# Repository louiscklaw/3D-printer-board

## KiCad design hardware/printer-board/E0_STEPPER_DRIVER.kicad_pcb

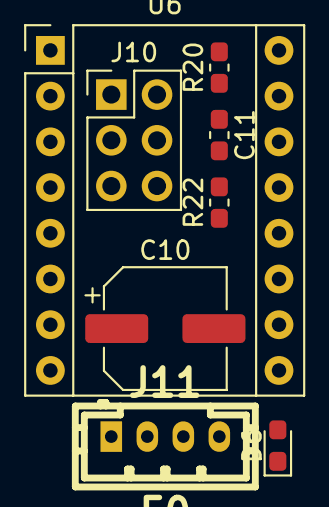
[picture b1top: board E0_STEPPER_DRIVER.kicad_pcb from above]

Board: 2 copper layers, 9 parts (1 on the bottom side), 13 nets, no tracks yet.

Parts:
C10: CP100uf,25V; CP_Elec_6.3x7.7
C11: C104,0603; C_0603_1608Metric_Pad1.05x0.95mm_HandSolder
D6: LED_BLUE,0603; LED_0603_1608Metric_Pad1.05x0.95mm_HandSolder
J10: MS_SELECT; PinHeader_2x03_P2.54mm_Vertical
J11: E0; b4b-ph-kl,stepper_terminal
R20: R104,0603; R_0603_1608Metric_Pad1.05x0.95mm_HandSolder
R21: R102,0603; R_0603_1608Metric_Pad1.05x0.95mm_HandSolder
R22: R103,0603; R_0603_1608Metric_Pad1.05x0.95mm_HandSolder
U6: A4988_MODULE; Pololu_Breakout-16_15.2x20.3mm

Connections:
+3V3_STM32: C11.2, J10.2, J10.4, J10.6, R21.1, R22.1, U6.10
+12V: C10.1, U6.16
/~E0_EN~: D6.1, R22.2, U6.1
GND: C10.2, C11.1, R20.1, U6.9, U6.15
unnamed: D6.2, R21.2
unnamed: J10.1, R20.2, U6.2
unnamed: J10.3, U6.3
unnamed: J10.5, U6.4
unnamed: J11.1, U6.14
unnamed: J11.2, U6.13
unnamed: J11.3, U6.12
unnamed: J11.4, U6.11
unnamed: U6.5, U6.6

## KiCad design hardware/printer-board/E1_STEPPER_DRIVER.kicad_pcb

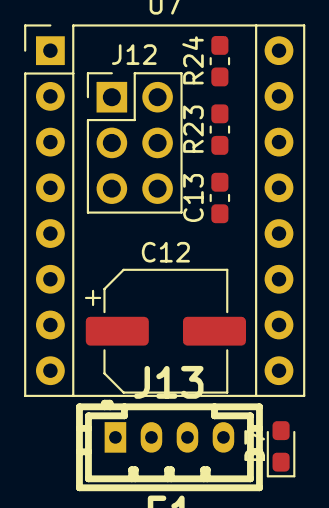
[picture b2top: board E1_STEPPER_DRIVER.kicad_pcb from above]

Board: 2 copper layers, 9 parts (1 on the bottom side), 13 nets, no tracks yet.

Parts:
C12: CP100uf,25V; CP_Elec_6.3x7.7
C13: C104,0603; C_0603_1608Metric_Pad1.05x0.95mm_HandSolder
D7: LED_BLUE,0603; LED_0603_1608Metric_Pad1.05x0.95mm_HandSolder
J12: MS_SELECT; PinHeader_2x03_P2.54mm_Vertical
J13: E1; b4b-ph-kl,stepper_terminal
R23: R104,0603; R_0603_1608Metric_Pad1.05x0.95mm_HandSolder
R24: R102,0603; R_0603_1608Metric_Pad1.05x0.95mm_HandSolder
R25: R103,0603; R_0603_1608Metric_Pad1.05x0.95mm_HandSolder
U7: A4988_MODULE; Pololu_Breakout-16_15.2x20.3mm

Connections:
+3V3_STM32: C13.2, J12.2, J12.4, J12.6, R24.1, R25.1, U7.10
+12V: C12.1, U7.16
/~E1_EN~: D7.1, R25.2, U7.1
GND: C12.2, C13.1, R23.1, U7.9, U7.15
unnamed: D7.2, R24.2
unnamed: J12.1, R23.2, U7.2
unnamed: J12.3, U7.3
unnamed: J12.5, U7.4
unnamed: J13.1, U7.14
unnamed: J13.2, U7.13
unnamed: J13.3, U7.12
unnamed: J13.4, U7.11
unnamed: U7.5, U7.6

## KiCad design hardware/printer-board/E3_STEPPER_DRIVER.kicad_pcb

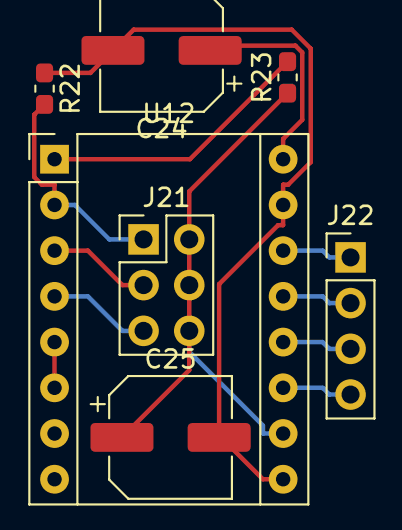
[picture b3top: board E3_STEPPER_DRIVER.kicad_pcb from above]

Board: 2 copper layers, 7 parts (0 on the bottom side), 12 nets.

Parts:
C24, C25: CP100uf,25V; CP_Elec_6.3x7.7
J21: MS_SELECT; PinHeader_2x03_P2.54mm_Vertical
J22: TO_MOTOR; PinHeader_1x04_P2.54mm_Vertical
R22: R104,0603; R_0603_1608Metric_Pad1.05x0.95mm_HandSolder
R23: R103,0603; R_0603_1608Metric_Pad1.05x0.95mm_HandSolder
U12: A4988_MODULE; Pololu_Breakout-16_15.2x20.3mm

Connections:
+5V: C25.1, J21.2, J21.4, J21.6, R23.1, U12.10
+12V: C24.1, U12.16
/~EN~: R23.2, U12.1
GND: C24.2, C25.2, R22.1, U12.9, U12.15
unnamed: J21.1, R22.2, U12.2
unnamed: J21.3, U12.3
unnamed: J21.5, U12.4
unnamed: J22.1, U12.14
unnamed: J22.2, U12.13
unnamed: J22.3, U12.12
unnamed: J22.4, U12.11
unnamed: U12.5, U12.6

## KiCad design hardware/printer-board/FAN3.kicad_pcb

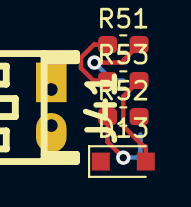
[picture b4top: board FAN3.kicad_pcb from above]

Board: 2 copper layers, 6 parts (1 on the bottom side), 4 nets.

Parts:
D13: 1N4148; D_SOD-323_HandSoldering
J41: TO FAN4; s2b-ph-kl,fan_output
Q1: SS9013_J3; SOT-23_Handsoldering
R51: R331; R_0603_1608Metric_Pad1.05x0.95mm_HandSolder
R52: R471; R_0603_1608Metric_Pad1.05x0.95mm_HandSolder
R53: R103; R_0603_1608Metric_Pad1.05x0.95mm_HandSolder

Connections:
/FAN_PWM_OUTPUT: Q1.3, R51.2
/STM32_FAN_RPM: D13.2, R53.2
unnamed: Q1.1, R52.1
VDD: R51.1, R53.1

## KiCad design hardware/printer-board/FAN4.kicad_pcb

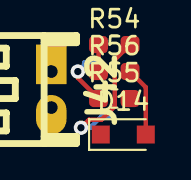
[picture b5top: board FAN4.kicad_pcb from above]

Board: 2 copper layers, 6 parts (1 on the bottom side), 4 nets.

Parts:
D14: 1N4148; D_SOD-323_HandSoldering
J42: TO FAN5; s2b-ph-kl,fan_output
Q1: SS9013_J3; SOT-23_Handsoldering
R54: R331; R_0603_1608Metric_Pad1.05x0.95mm_HandSolder
R55: R471; R_0603_1608Metric_Pad1.05x0.95mm_HandSolder
R56: R103; R_0603_1608Metric_Pad1.05x0.95mm_HandSolder

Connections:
/FAN_PWM_OUTPUT: Q1.3, R54.2
/STM32_FAN_RPM: D14.2, R56.2
unnamed: Q1.1, R55.1
VDD: R54.1, R56.1

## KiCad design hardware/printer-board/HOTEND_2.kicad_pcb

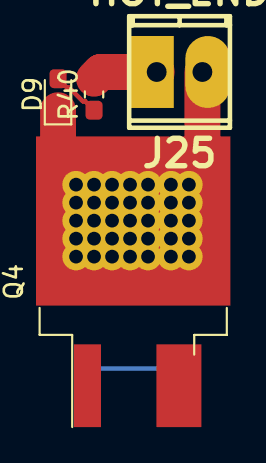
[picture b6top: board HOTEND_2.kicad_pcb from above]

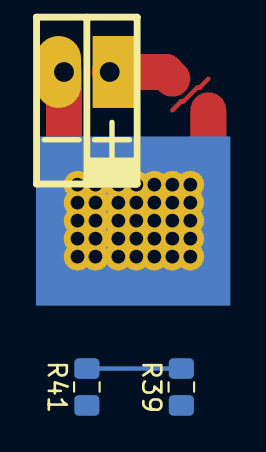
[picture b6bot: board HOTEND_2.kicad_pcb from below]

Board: 2 copper layers, 6 parts (2 on the bottom side), 6 nets.

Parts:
D9: LED_RED,0603; LED_0603_1608Metric_Pad1.05x0.95mm_HandSolder
J25: HOT_END; mpt_0,5%2f2-2,54,heatbed
Q4: WSK220N04; TO-263-2,drill_array
R39: R100,0805; R_0805_2012Metric_Pad1.15x1.40mm_HandSolder
R40: R182,0603; R_0603_1608Metric_Pad1.05x0.95mm_HandSolder
R41: R104,0805; R_0805_2012Metric_Pad1.15x1.40mm_HandSolder

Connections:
+12V: J25.1, R40.2
/-12V: D9.1, J25.2, Q4.2
/HOTEND_EN: R39.2, R41.2
GND: Q4.3, R41.1
unnamed: D9.2, R40.1
unnamed: Q4.1, R39.1

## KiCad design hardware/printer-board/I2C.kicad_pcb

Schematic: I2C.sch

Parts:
J37: Conn_01x04; PinHeader_1x04_P2.54mm_Vertical
R36, R37: R472,0603; R_0603_1608Metric_Pad1.05x0.95mm_HandSolder

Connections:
+5V: J37.1, R36.1, R37.1
/SCL: J37.4, R37.2
/SDA: J37.3, R36.2
GND: J37.2

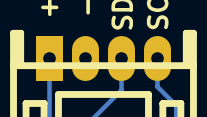
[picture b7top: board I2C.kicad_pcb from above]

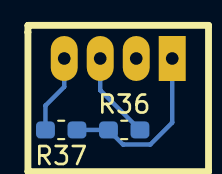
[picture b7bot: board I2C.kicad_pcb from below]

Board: 2 copper layers, 3 parts (2 on the bottom side), 3 nets.

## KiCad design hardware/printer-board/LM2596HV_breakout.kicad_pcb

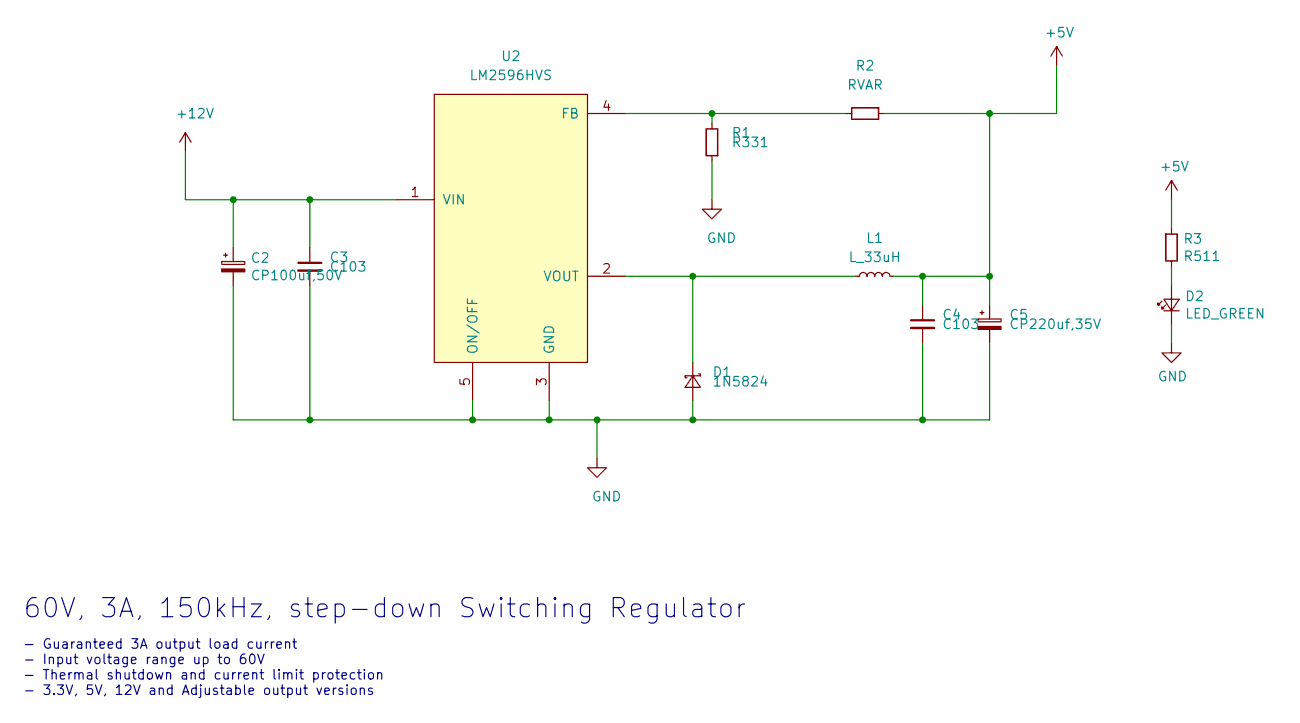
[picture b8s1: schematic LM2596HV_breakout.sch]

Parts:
C2: CP100uf,50V; C_0805_2012Metric_Pad1.15x1.40mm_HandSolder
C3: C103; C_0805_2012Metric_Pad1.15x1.40mm_HandSolder
C4: C103; c_elec_8x10.5
C5: CP220uf,35V; c_elec_8x10.5
D1: 1N5824; do214ac
D2: LED_GREEN; LED_0805_2012Metric_Pad1.15x1.40mm_HandSolder
L1: L_33uH; inductor_smd_12.5x7.5mm
R1: R331; R_0805_2012Metric_Pad1.15x1.40mm_HandSolder
R2: RVAR; R_0805_2012Metric_Pad1.15x1.40mm_HandSolder
R3: R511; R_0805_2012Metric_Pad1.15x1.40mm_HandSolder
U2: LM2596HVS; TO-263-5_TabPin3

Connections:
+5V: C4.1, C5.1, L1.2, R2.1, R3.1; also elsewhere on the board
+12V: C2.1, C3.1, U2.1 (VIN)
GND: C2.2, C3.2, C4.2, C5.2, D1.2 (A), D2.1 (K), R1.1, U2.3 (GND), U2.5 (ON/OFF); also elsewhere on the board
unnamed: D1.1 (K), L1.1, U2.2 (VOUT)
unnamed: D2.2 (A), R3.2
unnamed: R1.2, R2.2, U2.4 (FB)

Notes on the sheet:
60V, 3A, 150kHz, step-down Switching Regulator
- Guaranteed 3A output load current - Input voltage range up to 60V - Thermal shutdown and current limit protection - 3.3V, 5V, 12V and Adjustable output versions

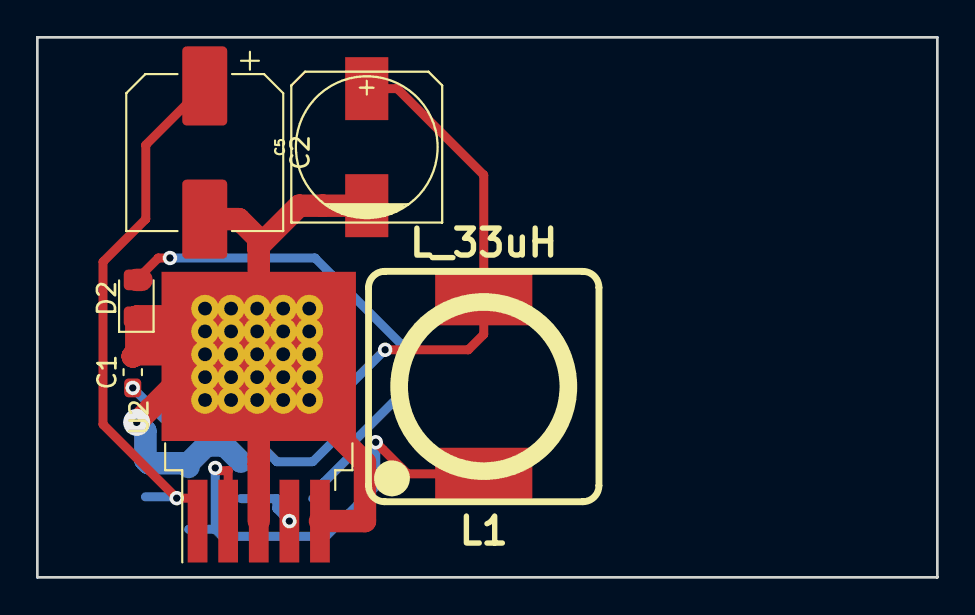
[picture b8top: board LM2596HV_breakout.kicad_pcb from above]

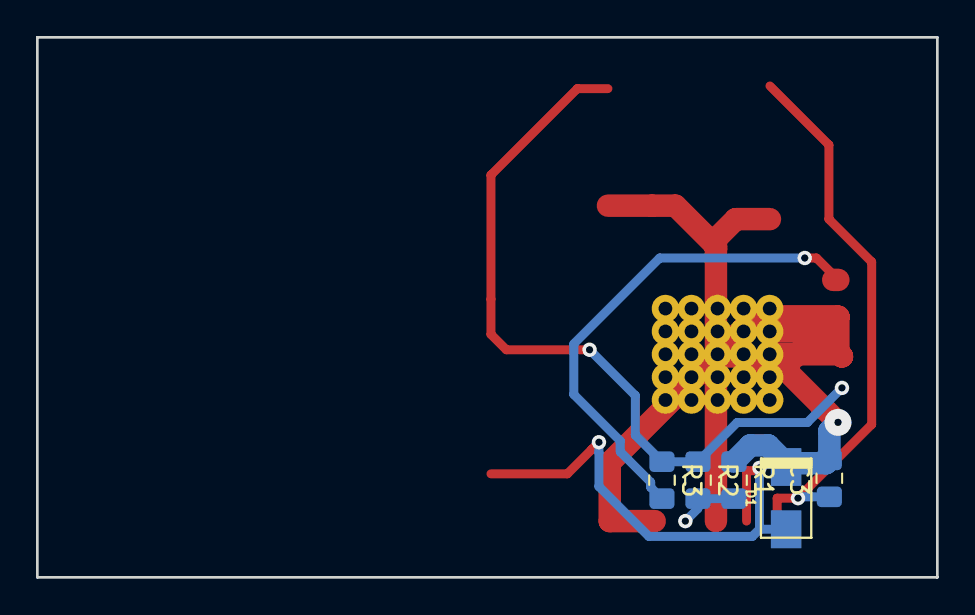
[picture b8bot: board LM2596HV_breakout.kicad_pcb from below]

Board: 2 copper layers, 50.0 x 30.0 mm, 11 parts (5 on the bottom side), 6 nets.

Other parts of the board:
C1: C103,0603; C_0603_1608Metric_Pad1.05x0.95mm_HandSolder

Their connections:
+5V: C1.1; also elsewhere on the board
GND: C1.2; also elsewhere on the board
